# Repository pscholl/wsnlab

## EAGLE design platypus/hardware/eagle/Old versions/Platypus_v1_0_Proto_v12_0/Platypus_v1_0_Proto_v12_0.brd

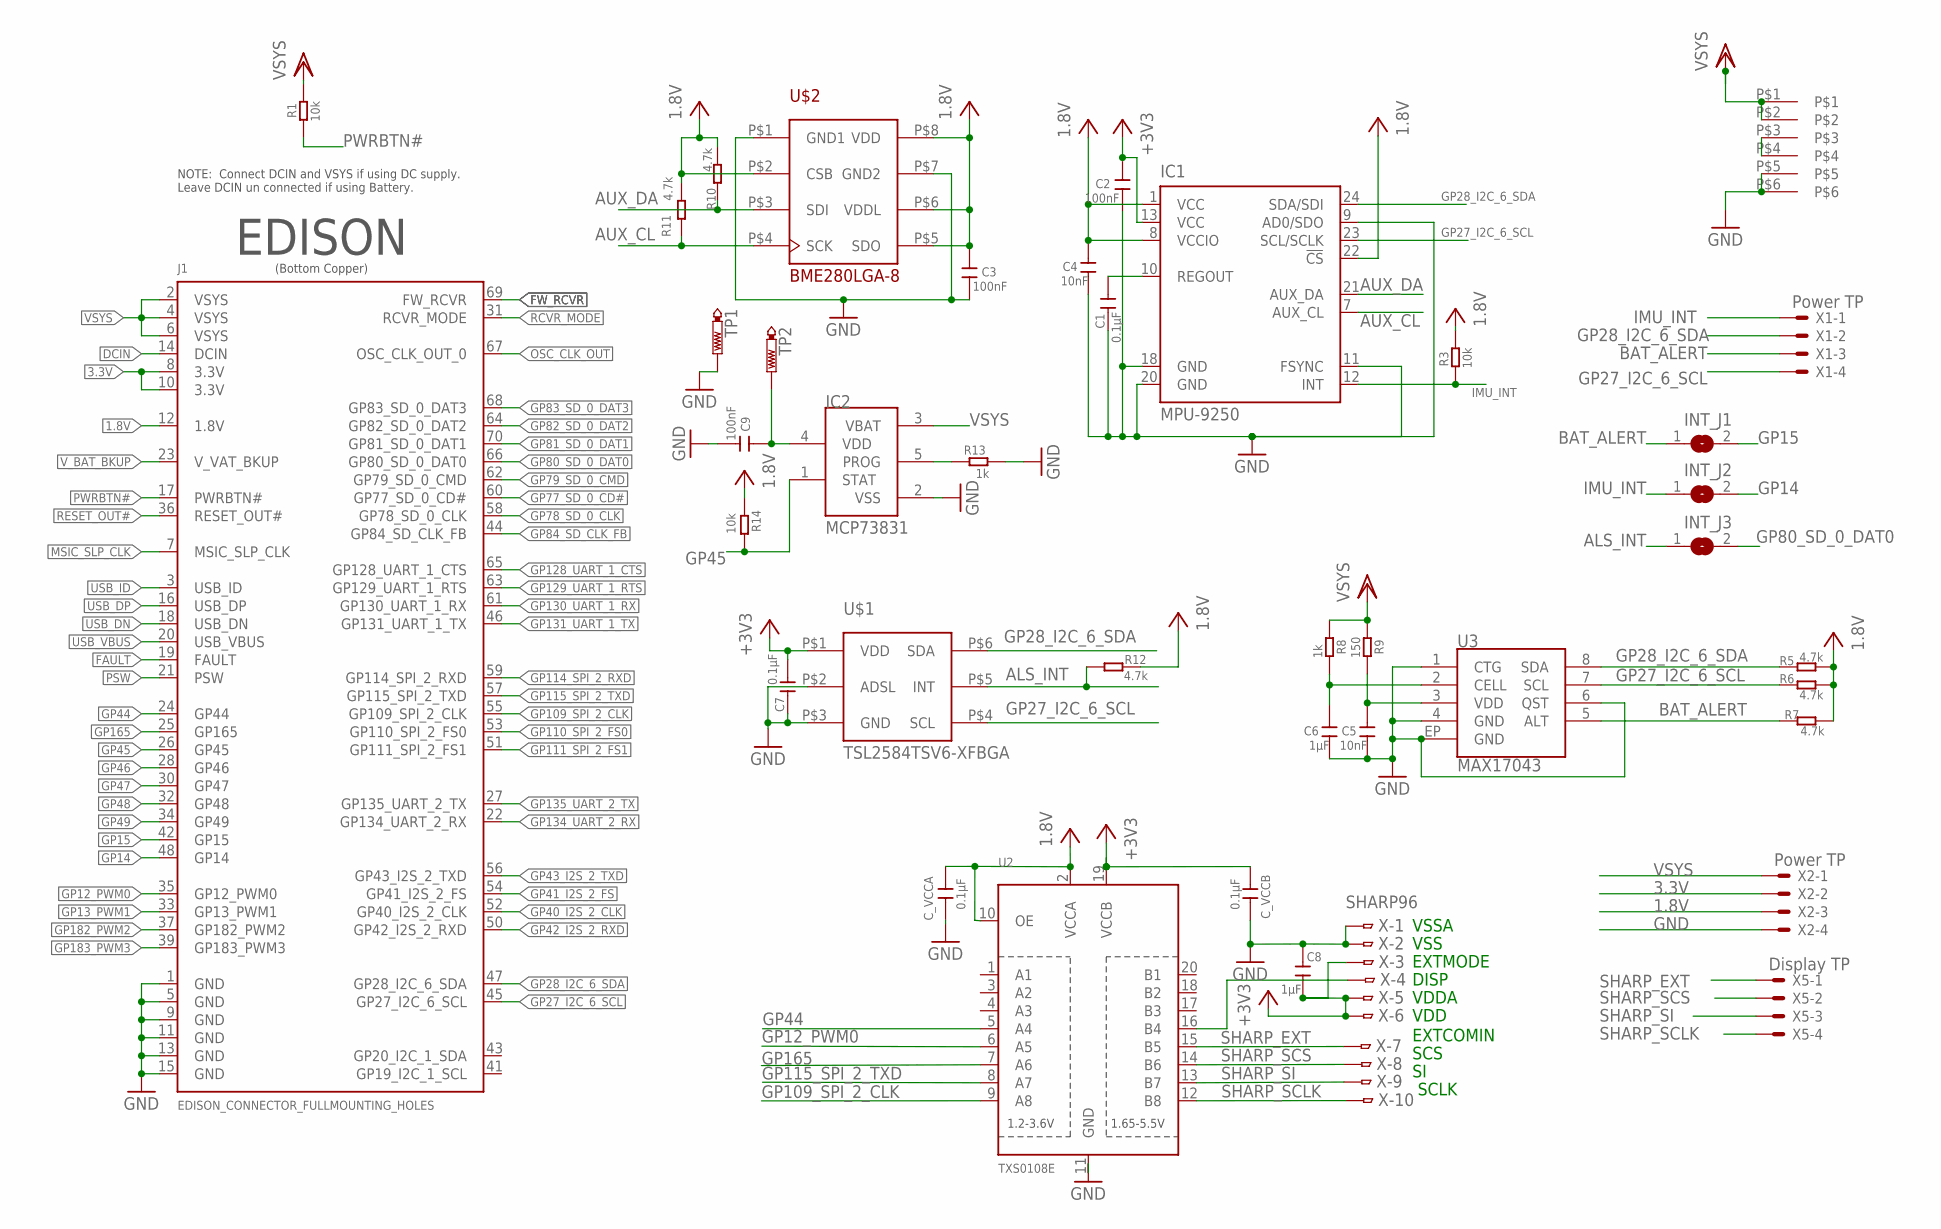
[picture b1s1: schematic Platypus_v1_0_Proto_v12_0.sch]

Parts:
C1, C7: 0.1µF; C0603
C2, C3, C9: 100nF; C0603
C4, C5: 10nF; C0603
C6, C8: 1µF; C0603
C_VCCA: 0.1µF; C0603
C_VCCB: 0.1µF; C0603
IC1: MPU-9250; QFN24-SMALL
IC2: MCP73831; SOT23-5L
INT_J1, INT_J2, INT_J3: SJ
J1: EDISON_CONNECTOR_FULLMOUNTING_HOLES; EDISON_DAUGHTER
R1, R3, R14: 10k; R0603
R5, R6, R7, R10, R11, R12: 4.7k; R0603
R8, R13: 1k; R0603
R9: 150; R0603
TP1, TP2: PTR1TP19SQ; TP19SQ
U2: TXS0108E; TSSOP20
U3: MAX17043; TDFN-8
U$1: TSL2584TSV6-XFBGA; 6-XFBGA
U$2: BME280LGA-8; LGA-8
U$3: HIROSE_BAT_CON; 0.5MM-PITCH,6-PIN
X: SHARP96; FH12-10S-0.5SH
X1, X2: Power TP; 53047-04
X5: Display TP; 53047-04

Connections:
1.8V: C3.2, C4.2, C_VCCA.2, IC1.1 (VCC), IC1.8 (VCCIO), IC1.22 (!CS), J1.12 (1.8V), R3.2, R5.2, R6.2, R7.1, R10.2, R11.2, R12.2, R14.2, U2.2 (VCCA), U2.10 (OE), U$2.P$2 (CSB), U$2.P$5 (SDO), U$2.P$6 (VDDL), U$2.P$8 (VDD), X2.3
3.3V: C2.2, C7.2, C8.1, C_VCCB.2, IC1.13 (VCC), J1.8 (3.3V), J1.10 (3.3V), U2.19 (VCCB), U$1.P$1 (VDD), X.3, X.5, X.6, X2.2
ALS_INT: INT_J3.1, R12.1, U$1.P$5 (INT)
AUX_CL: IC1.7 (AUX_CL), R11.1, U$2.P$4 (SCK)
AUX_DA: IC1.21 (AUX_DA), R10.1, U$2.P$3 (SDI)
BAT_ALERT: INT_J1.1, R7.2, U3.5 (ALT), X1.3
DCIN: J1.14 (DCIN)
FAULT: J1.19 (FAULT)
FW_RCVR: J1.69 (FW_RCVR)
GND: C1.1, C2.1, C3.1, C4.1, C5.1, C6.1, C7.1, C8.2, C9.1, C_VCCA.1, C_VCCB.1, IC1.9 (AD0/SDO), IC1.11 (FSYNC), IC1.18 (GND), IC1.20 (GND), IC2.2 (VSS), J1.1 (GND), J1.5 (GND), J1.9 (GND), J1.11 (GND), J1.13 (GND), J1.15 (GND), R13.1, TP1.TP, U2.11 (GND), U3.1 (CTG), U3.4 (GND), U3.6 (QST), U3.EP (GND), U$1.P$2 (ADSL), U$1.P$3 (GND), U$2.P$1 (GND1), U$2.P$7 (GND2), U$3.P$5, U$3.P$6, X.1, X.2, X2.4
GP12_PWM0: J1.35 (GP12_PWM0), U2.6 (A5)
GP13_PWM1: J1.33 (GP13_PWM1)
GP14: INT_J2.2, J1.48 (GP14)
GP15: INT_J1.2, J1.42 (GP15)
GP27_I2C_6_SCL: IC1.23 (SCL/SCLK), J1.45 (GP27_I2C_6_SCL), R6.1, U3.7 (SCL), U$1.P$4 (SCL), X1.4
GP28_I2C_6_SDA: IC1.24 (SDA/SDI), J1.47 (GP28_I2C_6_SDA), R5.1, U3.8 (SDA), U$1.P$6 (SDA), X1.2
GP40_I2S_2_CLK: J1.52 (GP40_I2S_2_CLK)
GP41_I2S_2_FS: J1.54 (GP41_I2S_2_FS)
GP42_I2S_2_RXD: J1.50 (GP42_I2S_2_RXD)
GP43_I2S_2_TXD: J1.56 (GP43_I2S_2_TXD)
GP44: J1.24 (GP44), U2.5 (A4)
GP45: IC2.1 (STAT), J1.26 (GP45), R14.1
GP46: J1.28 (GP46)
GP47: J1.30 (GP47)
GP48: J1.32 (GP48)
GP49: J1.34 (GP49)
GP77_SD_0_CD#: J1.60 (GP77_SD_0_CD#)
GP78_SD_0_CLK: J1.58 (GP78_SD_0_CLK)
GP79_SD_0_CMD: J1.62 (GP79_SD_0_CMD)
GP80_SD_0_DAT0: INT_J3.2, J1.66 (GP80_SD_0_DAT0)
GP81_SD_0_DAT1: J1.70 (GP81_SD_0_DAT1)
GP82_SD_0_DAT2: J1.64 (GP82_SD_0_DAT2)
GP83_SD_0_DAT3: J1.68 (GP83_SD_0_DAT3)
GP84_SD_CLK_FB: J1.44 (GP84_SD_CLK_FB)
GP109_SPI_2_CLK: J1.55 (GP109_SPI_2_CLK), U2.9 (A8)
GP110_SPI_2_FS0: J1.53 (GP110_SPI_2_FS0)
GP111_SPI_2_FS1: J1.51 (GP111_SPI_2_FS1)
GP114_SPI_2_RXD: J1.59 (GP114_SPI_2_RXD)
GP115_SPI_2_TXD: J1.57 (GP115_SPI_2_TXD), U2.8 (A7)
GP128_UART_1_CTS: J1.65 (GP128_UART_1_CTS)
GP129_UART_1_RTS: J1.63 (GP129_UART_1_RTS)
GP130_UART_1_RX: J1.61 (GP130_UART_1_RX)
GP131_UART_1_TX: J1.46 (GP131_UART_1_TX)
GP134_UART_2_RX: J1.22 (GP134_UART_2_RX)
GP135_UART_2_TX: J1.27 (GP135_UART_2_TX)
GP165: J1.25 (GP165), U2.7 (A6)
GP182_PWM2: J1.37 (GP182_PWM2)
GP183_PWM3: J1.39 (GP183_PWM3)
IMU_INT: IC1.12 (INT), INT_J2.1, R3.1, X1.1
MSIC_SLP_CLK: J1.7 (MSIC_SLP_CLK)
unnamed: IC2.5 (PROG), R13.2
unnamed: C1.2, IC1.10 (REGOUT)
unnamed: C6.2, R8.1, U3.2 (CELL)
unnamed: U2.16 (B4), X.4
unnamed: U$3.P$3, U$3.P$4
unnamed: C9.2, IC2.4 (VDD), TP2.TP
unnamed: C5.2, R9.1, U3.3 (VDD)
OSC_CLK_OUT: J1.67 (OSC_CLK_OUT_0)
PSW: J1.21 (PSW)
PWRBTN#: J1.17 (PWRBTN#), R1.1
RCVR_MODE: J1.31 (RCVR_MODE)
RESET_OUT#: J1.36 (RESET_OUT#)
SHARP_EXT: U2.15 (B5), X.7, X5.1
SHARP_SCLK: U2.12 (B8), X.10, X5.4
SHARP_SCS: U2.14 (B6), X.8, X5.2
SHARP_SI: U2.13 (B7), X.9, X5.3
USB_DN: J1.18 (USB_DN)
USB_DP: J1.16 (USB_DP)
USB_ID: J1.3 (USB_ID)
USB_VBUS: J1.20 (USB_VBUS)
VSYS: IC2.3 (VBAT), J1.2 (VSYS), J1.4 (VSYS), J1.6 (VSYS), R1.2, R8.2, R9.2, U$3.P$1, U$3.P$2, X2.1
V_BAT_BKUP: J1.23 (V_VAT_BKUP)

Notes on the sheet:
EDISON
(Bottom Copper)
NOTE: Connect DCIN and VSYS if using DC supply. Leave DCIN un connected if using Battery.
VSSA
VSS
EXTMODE
DISP
VDDA
VDD
EXTCOMIN
SCS
SCLK

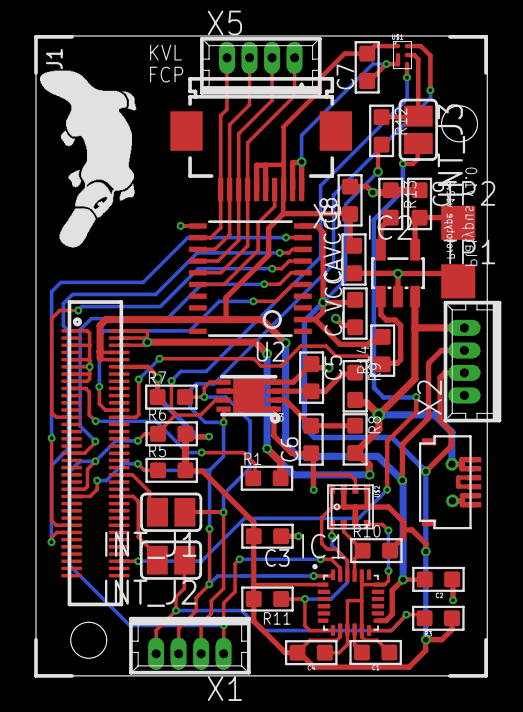
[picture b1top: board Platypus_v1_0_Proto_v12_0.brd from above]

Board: 2 copper layers, 25.1 x 35.5 mm, 40 parts (0 on the bottom side), 32 nets.

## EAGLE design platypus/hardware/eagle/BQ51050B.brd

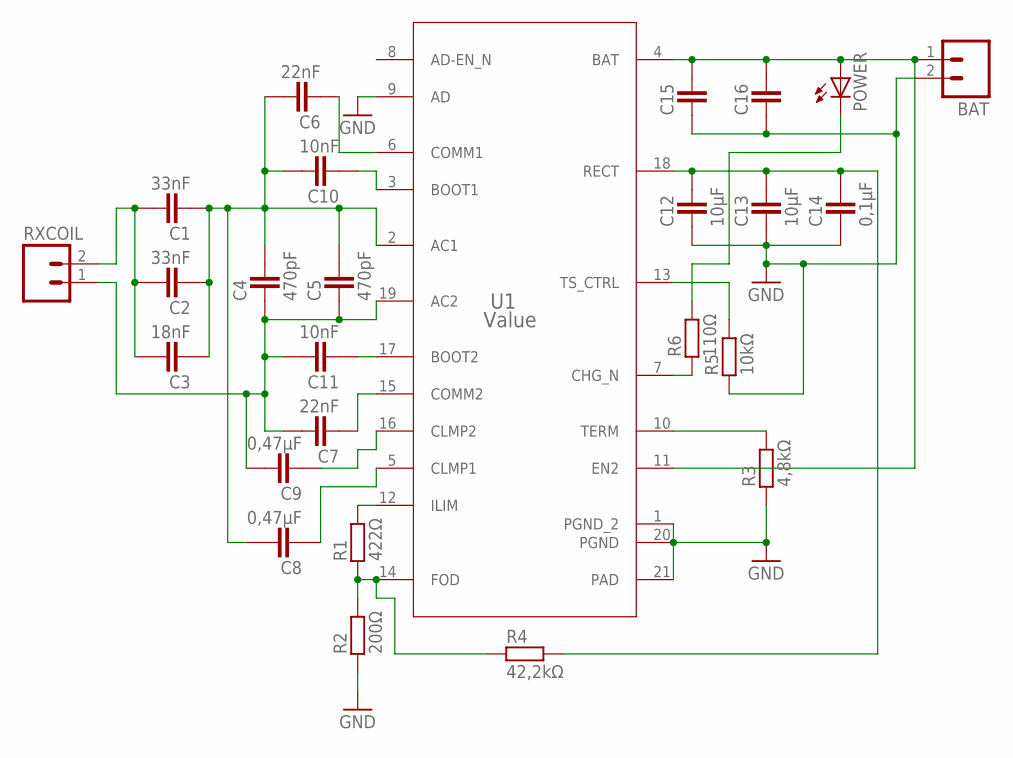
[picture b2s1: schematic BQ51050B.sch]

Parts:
BAT: M02LOCK; 1X02_LOCK
C1, C2: 33nF; CAPC1005X60N
C3: 18nF; CAPC1005X60N
C4, C5: 470pF; CAPC1005X60N
C6, C7: 22nF; CAPC1005X60N
C8, C9: 0,47µF; CAPC1005X60N
C10, C11: 10nF; CAPC1005X60N
C12, C13: 10µF; CAPC1608X92N
C14: 0,1µF; CAPC1005X60N
C15, C16: CAPACITOR_0402; CAPC1005X60N
POWER: LEDSML0603; SML0603
R1: 422Ω; RESC1005X40AN
R2: 200Ω; RESC1005X40AN
R3: 4,8kΩ; RESC1005X40AN
R4: 42,2kΩ; RESC1005X40AN
R5: 10kΩ; RESC1005X40AN
R6: 110Ω; RESC1005X40AN
RXCOIL: M02LOCK; 1X02_LOCK
U1: Value; RHL0020A

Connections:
GND: BAT.2, C12.1, C13.1, C14.1, C15.1, C16.1, R2.1, R3.1, R5.1, U1.1 (PGND_2), U1.9 (AD), U1.20 (PGND), U1.21 (PAD)
unnamed: C1.2, C2.2, C3.2, RXCOIL.2
unnamed: C12.2, C13.2, C14.2, R4.2, U1.18 (RECT)
unnamed: C1.1, C2.1, C3.1, C4.2, C5.2, C6.2, C8.2, C10.2, U1.2 (AC1)
unnamed: R1.2, U1.12 (ILIM)
unnamed: C4.1, C5.1, C7.2, C9.2, C11.2, RXCOIL.1, U1.19 (AC2)
unnamed: BAT.1, C15.2, C16.2, POWER.A, U1.4 (BAT), U1.11 (EN2)
unnamed: C6.1, U1.6 (COMM1)
unnamed: C7.1, U1.15 (COMM2)
unnamed: C8.1, U1.5 (CLMP1)
unnamed: C9.1, U1.16 (CLMP2)
unnamed: C10.1, U1.3 (BOOT1)
unnamed: C11.1, U1.17 (BOOT2)
unnamed: R1.1, R2.2, R4.1, U1.14 (FOD)
unnamed: R3.2, U1.10 (TERM)
unnamed: R5.2, U1.13 (TS_CTRL)
unnamed: POWER.C, R6.2
unnamed: R6.1, U1.7 (CHG_N)

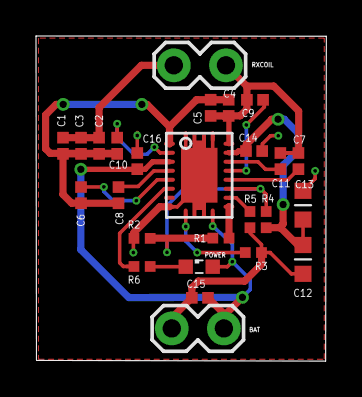
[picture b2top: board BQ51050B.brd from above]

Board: 2 copper layers, 16.1 x 18.1 mm, 26 parts (0 on the bottom side), 18 nets.

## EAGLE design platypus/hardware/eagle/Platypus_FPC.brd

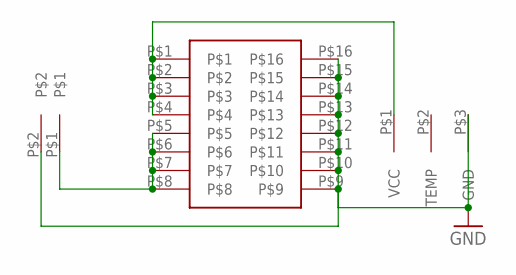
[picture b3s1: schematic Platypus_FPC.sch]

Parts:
U$1: BM10B(0.8)-16DP-0.4V(51); 16-HEADER
U$2: PLATY_BAT_PAD; FPC-6
U$3: PLATY_CHARGER_CON; 2-PAD

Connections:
GND: U$1.P$9, U$1.P$10, U$1.P$11, U$1.P$12, U$1.P$13, U$1.P$14, U$1.P$15, U$1.P$16, U$2.P$3 (GND), U$3.P$2
unnamed: U$1.P$1, U$1.P$2, U$1.P$3, U$1.P$4, U$2.P$1 (VCC)
unnamed: U$1.P$5, U$1.P$6, U$1.P$7, U$1.P$8, U$3.P$1

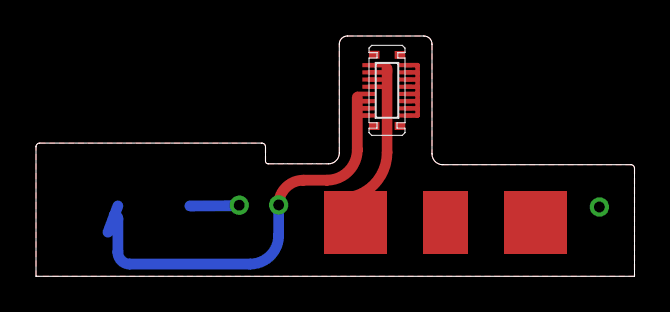
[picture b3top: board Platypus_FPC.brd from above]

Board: 2 copper layers, 33.2 x 13.4 mm, 3 parts (0 on the bottom side), 3 nets.

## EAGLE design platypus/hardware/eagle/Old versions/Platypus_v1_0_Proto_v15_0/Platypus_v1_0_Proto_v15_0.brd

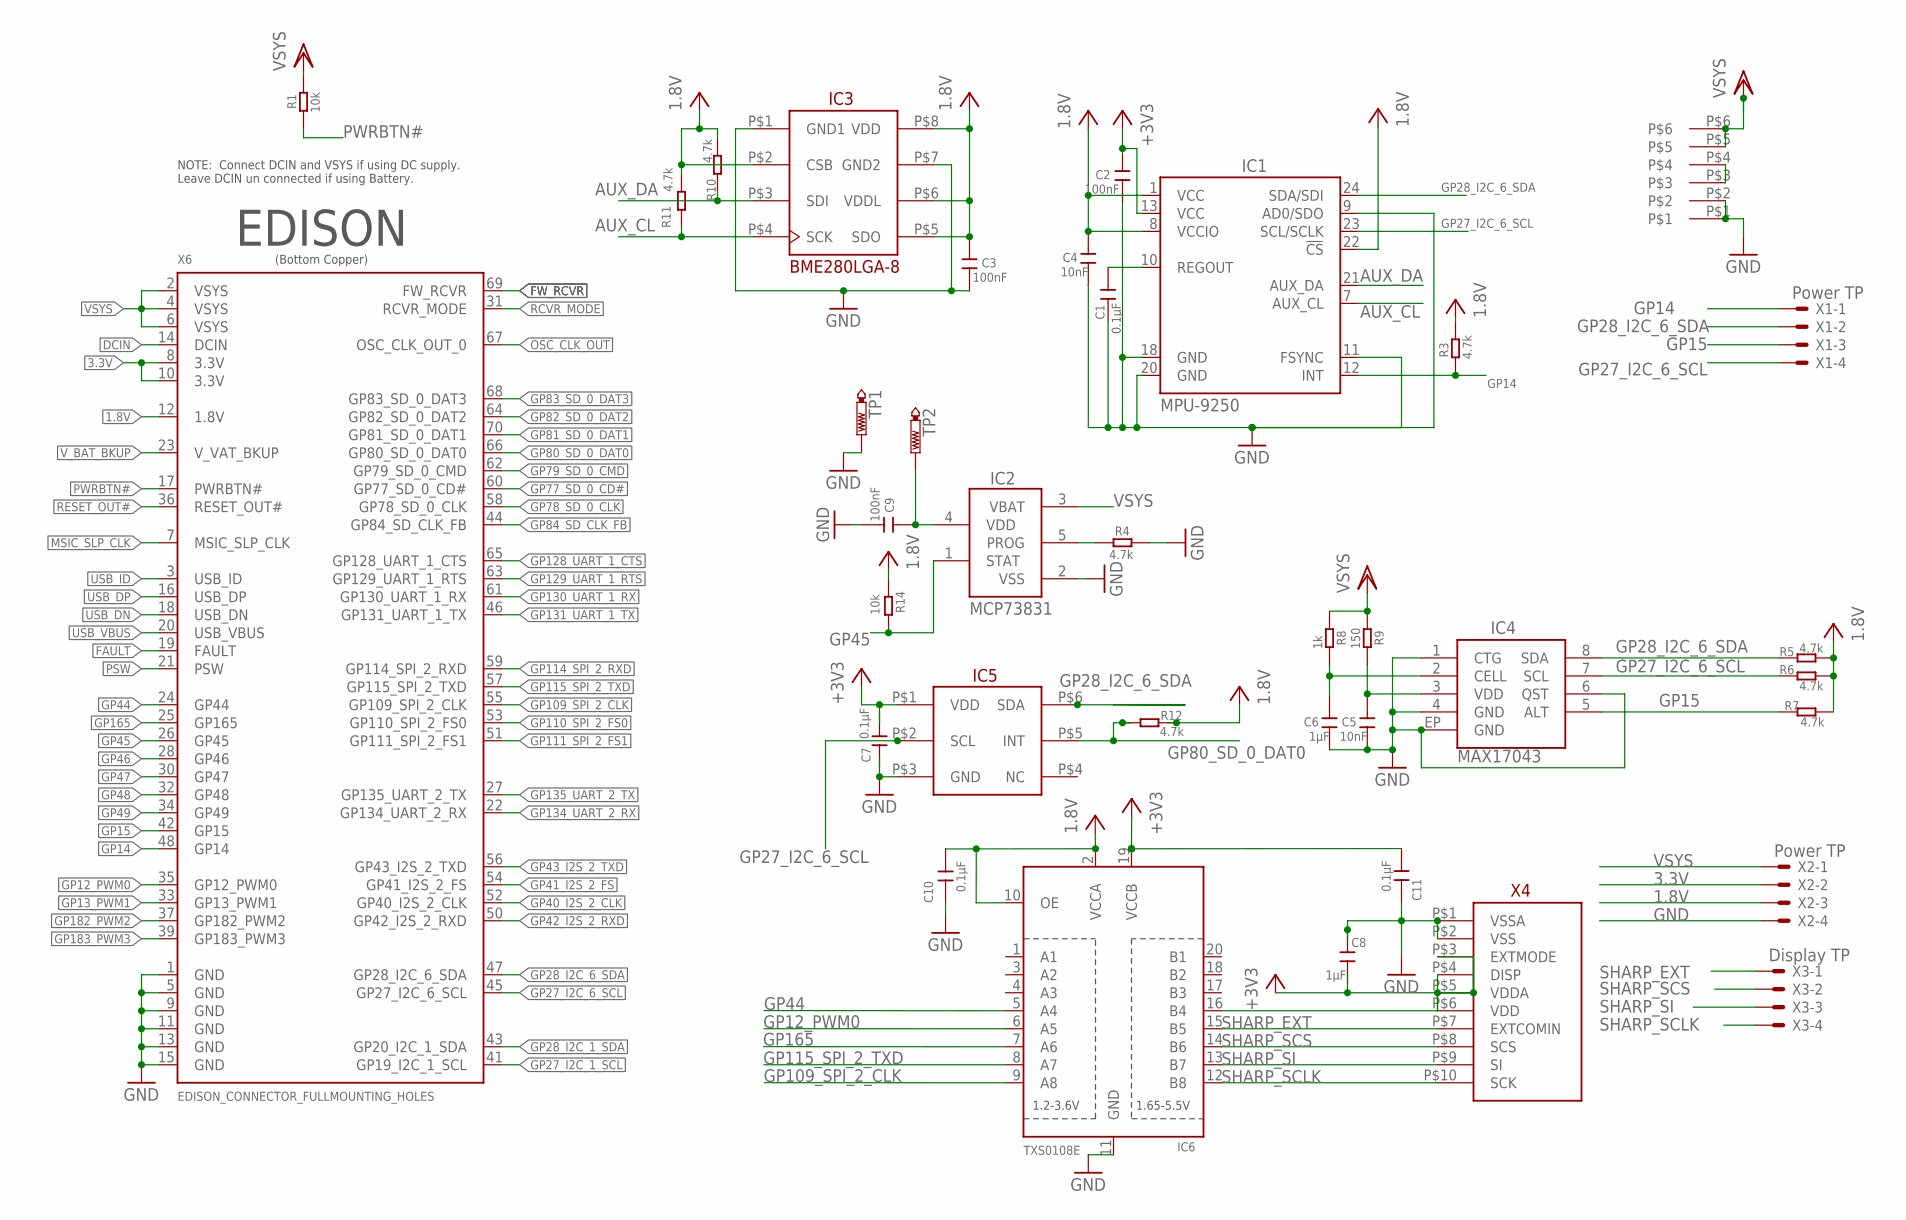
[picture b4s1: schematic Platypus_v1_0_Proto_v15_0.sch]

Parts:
C1, C7, C10, C11: 0.1µF; C0603
C2, C3, C9: 100nF; C0603
C4, C5: 10nF; C0603
C6, C8: 1µF; C0603
IC1: MPU-9250; QFN24-SMALL
IC2: MCP73831; SOT23-5L
IC3: BME280LGA-8; LGA-8
IC4: MAX17043; TDFN-8
IC5: TSL25723FNFN-6PIN; FN-6PIN
IC6: TXS0108E; TSSOP20
R1, R14: 10k; R0603
R3, R4, R5, R6, R7, R10, R11, R12: 4.7k; R0603
R8: 1k; R0603
R9: 150; R0603
TP1, TP2: PTR1TP19SQ; TP19SQ
U$3: HIROSE_BAT_CON; 0.5MM-PITCH,6-PIN
X1, X2: Power TP; 53047-04
X3: Display TP; 53047-04
X4: FH34SRJ-10S-0.5SH(50)FRC-10PIN-0.5MM; FRC-10PIN-0.5MM
X6: EDISON_CONNECTOR_FULLMOUNTING_HOLES; EDISON_DAUGHTER

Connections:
1.8V: C3.2, C4.2, C10.2, IC1.1 (VCC), IC1.8 (VCCIO), IC1.22 (!CS), IC3.P$2 (CSB), IC3.P$5 (SDO), IC3.P$6 (VDDL), IC3.P$8 (VDD), IC6.2 (VCCA), IC6.10 (OE), R3.2, R5.2, R6.2, R7.1, R10.2, R11.2, R12.2, R14.2, X2.3, X6.12 (1.8V)
3.3V: C2.2, C7.2, C11.2, IC1.13 (VCC), IC5.P$1 (VDD), IC6.19 (VCCB), X2.2, X4.P$3 (EXTMODE), X4.P$5 (VDDA), X4.P$6 (VDD), X6.8 (3.3V), X6.10 (3.3V)
AUX_CL: IC1.7 (AUX_CL), IC3.P$4 (SCK), R11.1
AUX_DA: IC1.21 (AUX_DA), IC3.P$3 (SDI), R10.1
DCIN: X6.14 (DCIN)
FAULT: X6.19 (FAULT)
FW_RCVR: X6.69 (FW_RCVR)
GND: C1.1, C2.1, C3.1, C4.1, C5.1, C6.1, C7.1, C8.2, C9.1, C10.1, C11.1, IC1.9 (AD0/SDO), IC1.11 (FSYNC), IC1.18 (GND), IC1.20 (GND), IC2.2 (VSS), IC3.P$1 (GND1), IC3.P$7 (GND2), IC4.1 (CTG), IC4.4 (GND), IC4.6 (QST), IC4.EP (GND), IC5.P$3 (GND), IC6.11 (GND), R4.1, TP1.TP, U$3.P$1, U$3.P$2, X2.4, X4.P$1 (VSSA), X4.P$2 (VSS), X6.1 (GND), X6.5 (GND), X6.9 (GND), X6.11 (GND), X6.13 (GND), X6.15 (GND)
GP12_PWM0: IC6.6 (A5), X6.35 (GP12_PWM0)
GP13_PWM1: X6.33 (GP13_PWM1)
GP14: IC1.12 (INT), R3.1, X1.1, X6.48 (GP14)
GP15: IC4.5 (ALT), R7.2, X1.3, X6.42 (GP15)
GP27_I2C_1_SCL: X6.41 (GP19_I2C_1_SCL)
GP27_I2C_6_SCL: IC1.23 (SCL/SCLK), IC4.7 (SCL), IC5.P$2 (SCL), R6.1, X1.4, X6.45 (GP27_I2C_6_SCL)
GP28_I2C_1_SDA: X6.43 (GP20_I2C_1_SDA)
GP28_I2C_6_SDA: IC1.24 (SDA/SDI), IC4.8 (SDA), IC5.P$6 (SDA), R5.1, X1.2, X6.47 (GP28_I2C_6_SDA)
GP40_I2S_2_CLK: X6.52 (GP40_I2S_2_CLK)
GP41_I2S_2_FS: X6.54 (GP41_I2S_2_FS)
GP42_I2S_2_RXD: X6.50 (GP42_I2S_2_RXD)
GP43_I2S_2_TXD: X6.56 (GP43_I2S_2_TXD)
GP44: IC6.5 (A4), X6.24 (GP44)
GP45: IC2.1 (STAT), R14.1, X6.26 (GP45)
GP46: X6.28 (GP46)
GP47: X6.30 (GP47)
GP48: X6.32 (GP48)
GP49: X6.34 (GP49)
GP77_SD_0_CD#: X6.60 (GP77_SD_0_CD#)
GP78_SD_0_CLK: X6.58 (GP78_SD_0_CLK)
GP79_SD_0_CMD: X6.62 (GP79_SD_0_CMD)
GP80_SD_0_DAT0: IC5.P$5 (INT), R12.1, X6.66 (GP80_SD_0_DAT0)
GP81_SD_0_DAT1: X6.70 (GP81_SD_0_DAT1)
GP82_SD_0_DAT2: X6.64 (GP82_SD_0_DAT2)
GP83_SD_0_DAT3: X6.68 (GP83_SD_0_DAT3)
GP84_SD_CLK_FB: X6.44 (GP84_SD_CLK_FB)
GP109_SPI_2_CLK: IC6.9 (A8), X6.55 (GP109_SPI_2_CLK)
GP110_SPI_2_FS0: X6.53 (GP110_SPI_2_FS0)
GP111_SPI_2_FS1: X6.51 (GP111_SPI_2_FS1)
GP114_SPI_2_RXD: X6.59 (GP114_SPI_2_RXD)
GP115_SPI_2_TXD: IC6.8 (A7), X6.57 (GP115_SPI_2_TXD)
GP128_UART_1_CTS: X6.65 (GP128_UART_1_CTS)
GP129_UART_1_RTS: X6.63 (GP129_UART_1_RTS)
GP130_UART_1_RX: X6.61 (GP130_UART_1_RX)
GP131_UART_1_TX: X6.46 (GP131_UART_1_TX)
GP134_UART_2_RX: X6.22 (GP134_UART_2_RX)
GP135_UART_2_TX: X6.27 (GP135_UART_2_TX)
GP165: IC6.7 (A6), X6.25 (GP165)
GP182_PWM2: X6.37 (GP182_PWM2)
GP183_PWM3: X6.39 (GP183_PWM3)
MSIC_SLP_CLK: X6.7 (MSIC_SLP_CLK)
unnamed: IC2.5 (PROG), R4.2
unnamed: C1.2, IC1.10 (REGOUT)
unnamed: C6.2, IC4.2 (CELL), R8.1
unnamed: IC6.16 (B4), X4.P$4 (DISP)
unnamed: U$3.P$3, U$3.P$4
unnamed: C9.2, IC2.4 (VDD), TP2.TP
unnamed: C5.2, IC4.3 (VDD), R9.1
OSC_CLK_OUT: X6.67 (OSC_CLK_OUT_0)
PSW: X6.21 (PSW)
PWRBTN#: R1.1, X6.17 (PWRBTN#)
RCVR_MODE: X6.31 (RCVR_MODE)
RESET_OUT#: X6.36 (RESET_OUT#)
SHARP_EXT: IC6.15 (B5), X3.1, X4.P$7 (EXTCOMIN)
SHARP_SCLK: IC6.12 (B8), X3.4, X4.P$10 (SCK)
SHARP_SCS: IC6.14 (B6), X3.2, X4.P$8 (SCS)
SHARP_SI: IC6.13 (B7), X3.3, X4.P$9 (SI)
USB_DN: X6.18 (USB_DN)
USB_DP: X6.16 (USB_DP)
USB_ID: X6.3 (USB_ID)
USB_VBUS: X6.20 (USB_VBUS)
VSYS: IC2.3 (VBAT), R1.2, R8.2, R9.2, U$3.P$5, U$3.P$6, X2.1, X6.2 (VSYS), X6.4 (VSYS), X6.6 (VSYS)
V_BAT_BKUP: X6.23 (V_VAT_BKUP)

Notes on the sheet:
EDISON
(Bottom Copper)
NOTE: Connect DCIN and VSYS if using DC supply. Leave DCIN un connected if using Battery.

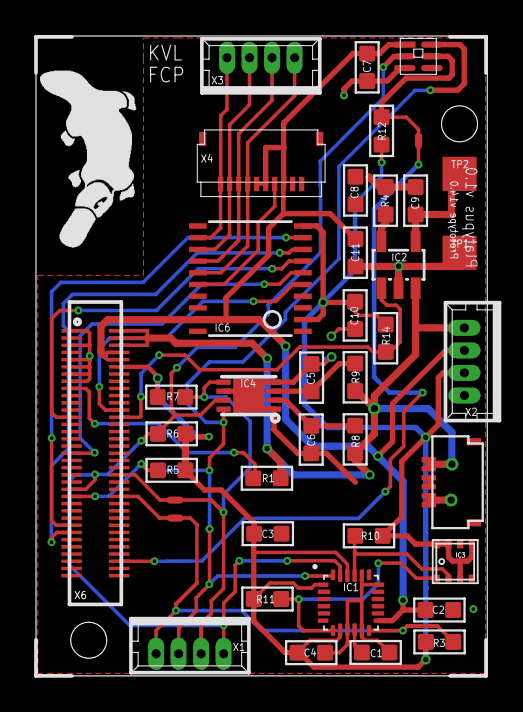
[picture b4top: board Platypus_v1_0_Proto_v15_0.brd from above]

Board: 2 copper layers, 25.1 x 35.5 mm, 37 parts (0 on the bottom side), 29 nets.

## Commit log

2015-12-04 add platypus code
2015-12-11 update platypus
2016-01-13 updated platypus hardware folder
2016-01-13 updated platypus firmware folder
2016-01-13 fixed some stuff to make display drivers usable in C
2016-01-27 updated platypus firmware (display/imu stuff, test code)
2016-02-16 add team results
2016-10-07 removed platypus folder in preparation for newest version, better do full cleanup since history isn't preserved here anyway
2016-10-07 added most recent version of internal platypus project
2016-10-07 removed a bunch of unnecessary stuff
2016-10-07 updated cmake/install.sh
2016-10-07 changed i2cbus + dspres
2016-10-07 config
2016-10-11 removed obsolete bat test
2016-10-11 platypus conf
2016-11-11 Header files must not be includes as source files. Otherwise, gcc generates PCH files which will be included in the *.a files.
    Also, have one big platypus library instead of 4 small ones.
2016-11-11 Added script to create tarball with all necessary files.
2016-11-11 Added a few files to tarball.
2016-11-11 there is a lib folder now
2016-11-17 reworked cmake file a bit. cmake is now doing release build by default
2016-11-17 there is no global Graphics Context
2016-11-17 there are no global contexts
2016-11-17 use provided contexts instead of global one
2016-11-17 drop const where necessary
2016-11-17 allow const char* for strings
2016-11-17 make strings const char* instead of int8_t*
2016-11-17 Revert "there is no global Graphics Context"
    This reverts commit be5e7955f4123f3cd2a5568d364c3ff2ba479ef3.
2016-11-17 added missing extern "C" (linker failed)
2016-11-17 remove header of missing platypus class
2016-11-17 new LCD driver and grlib C++ Wrapper
2016-11-17 build new lcdTest
2016-11-17 no need to define NDEBUG, it's set by cmake release build
2016-11-18 information about GrLib
2016-11-18 hold locks less long, allow for more time to render to buffer
2016-11-18 add new files to tarball
2016-11-18 cmdBufIndex is only written by main thread, no need to obtain lock first
2016-11-18 forgot to include <string>
2016-11-18 fix exception on join of enable() wasn't called
2016-11-18 more bad news about grlib
2016-11-18 avoid errors in STL headers by moving the defines of min and max
2016-11-18 script for source tarball
2016-11-18 also test drawLine and swapped back/foregroundcolor
2016-11-18 adjusted lcdTest a bit
2017-02-03 network broadcasting LCD driver
2017-02-03 use non-blocking io
2017-08-07 added Eclipse files

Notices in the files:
parts and their libraries:
SparkFun-Connectors: Licensing: Creative Commons ShareAlike 4.0 International - https://creativecommons.org/licenses/by-sa/4.0
